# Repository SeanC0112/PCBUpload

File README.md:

# PCBUpload
Upload of my PCB files for my quadruped robot

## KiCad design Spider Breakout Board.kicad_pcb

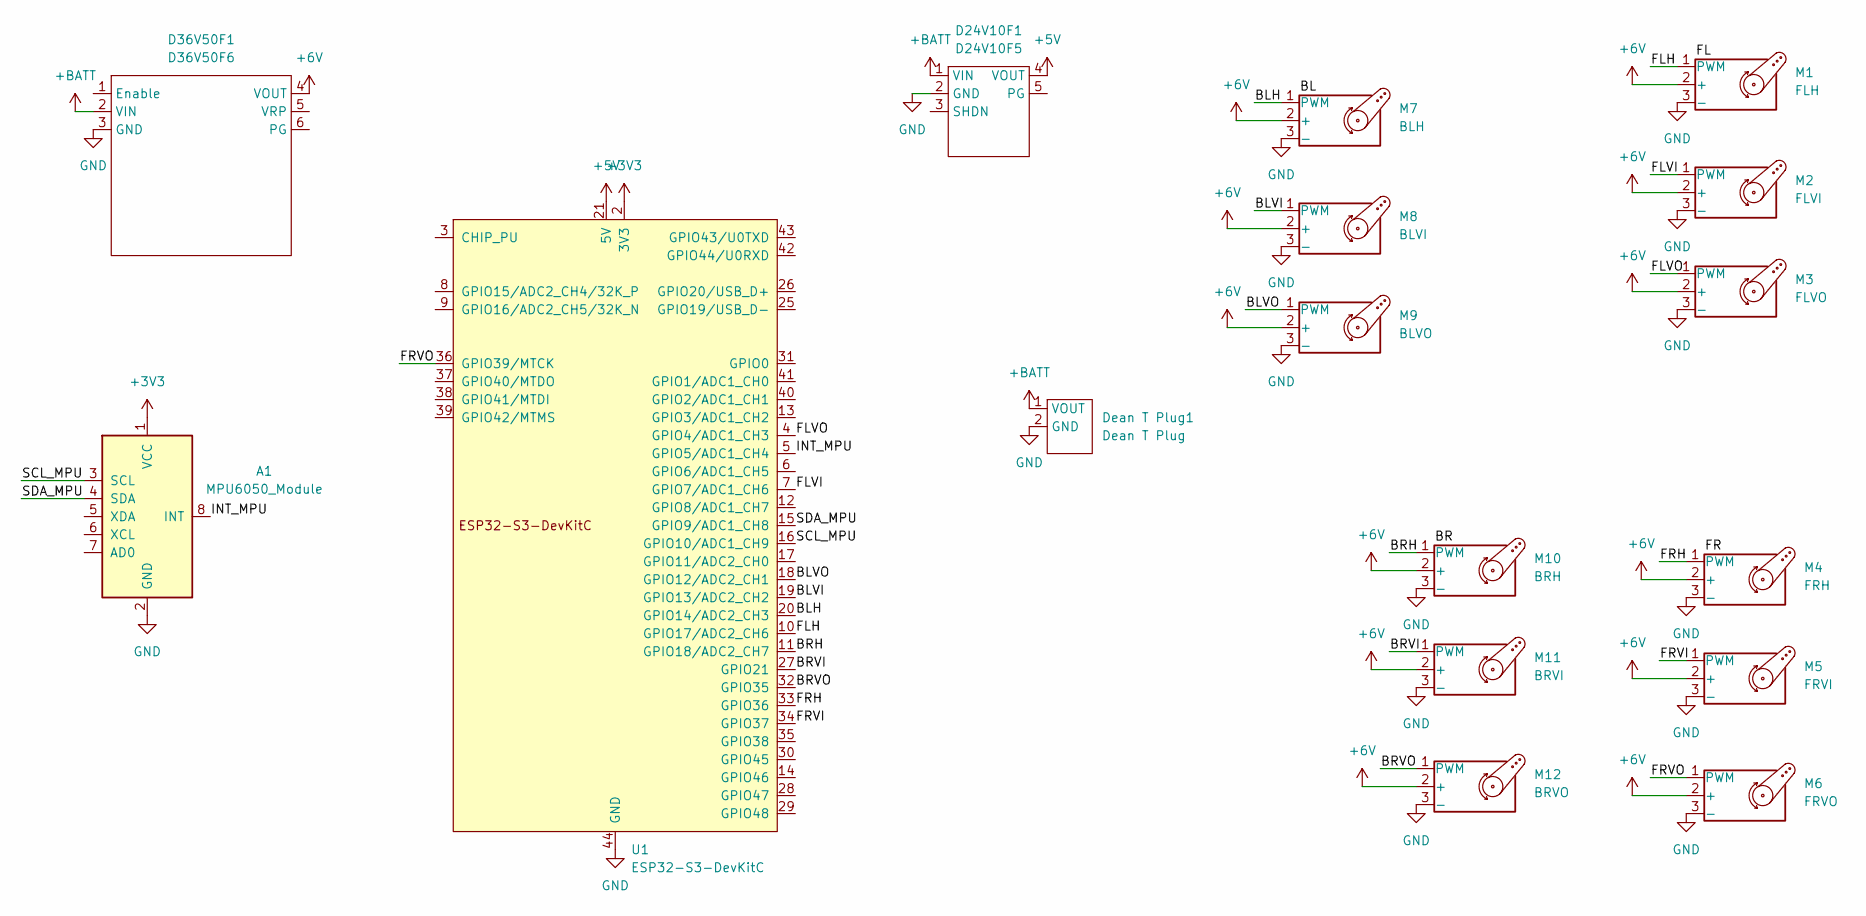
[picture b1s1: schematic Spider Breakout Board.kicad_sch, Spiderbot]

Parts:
A1: MPU6050_Module
D24V10F1: D24V10F5
D36V50F1: D36V50F6
Dean T Plug1: Dean T Plug; DEANS
M1: FLH; PinHeader_1x03_P2.54mm_Vertical
M2: FLVI; PinHeader_1x03_P2.54mm_Vertical
M3: FLVO; PinHeader_1x03_P2.54mm_Vertical
M4: FRH; PinHeader_1x03_P2.54mm_Vertical
M5: FRVI; PinHeader_1x03_P2.54mm_Vertical
M6: FRVO; PinHeader_1x03_P2.54mm_Vertical
M7: BLH; PinHeader_1x03_P2.54mm_Vertical
M8: BLVI; PinHeader_1x03_P2.54mm_Vertical
M9: BLVO; PinHeader_1x03_P2.54mm_Vertical
M10: BRH; PinHeader_1x03_P2.54mm_Vertical
M11: BRVI; PinHeader_1x03_P2.54mm_Vertical
M12: BRVO; PinHeader_1x03_P2.54mm_Vertical
U1: ESP32-S3-DevKitC

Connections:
+3V3: A1.1 (VCC), U1.1 (3V3), U1.2 (3V3)
+5V: D24V10F1.4 (VOUT), U1.21 (5V)
+6V: D36V50F1.4 (VOUT), M1.2 (+), M2.2 (+), M3.2 (+), M4.2 (+), M5.2 (+), M6.2 (+), M7.2 (+), M8.2 (+), M9.2 (+), M10.2 (+), M11.2 (+), M12.2 (+)
+BATT: D24V10F1.1 (VIN), D36V50F1.2 (VIN), Dean T Plug1.1 (VOUT)
/BLH: M7.1 (PWM), U1.20 (GPIO14/ADC2_CH3)
/BLVI: M8.1 (PWM), U1.19 (GPIO13/ADC2_CH2)
/BLVO: M9.1 (PWM), U1.18 (GPIO12/ADC2_CH1)
/BRH: M10.1 (PWM), U1.11 (GPIO18/ADC2_CH7)
/BRVI: M11.1 (PWM), U1.27 (GPIO21)
/BRVO: M12.1 (PWM), U1.32 (GPIO35)
/FLH: M1.1 (PWM), U1.10 (GPIO17/ADC2_CH6)
/FLVI: M2.1 (PWM), U1.7 (GPIO7/ADC1_CH6)
/FLVO: M3.1 (PWM), U1.4 (GPIO4/ADC1_CH3)
/FRH: M4.1 (PWM), U1.33 (GPIO36)
/FRVI: M5.1 (PWM), U1.34 (GPIO37)
/FRVO: M6.1 (PWM), U1.36 (GPIO39/MTCK)
/INT_MPU: A1.8 (INT), U1.5 (GPIO5/ADC1_CH4)
/SCL_MPU: A1.3 (SCL), U1.16 (GPIO10/ADC1_CH9)
/SDA_MPU: A1.4 (SDA), U1.15 (GPIO9/ADC1_CH8)
GND: A1.2 (GND), D24V10F1.2 (GND), D36V50F1.3 (GND), Dean T Plug1.2 (GND), M1.3 (-), M2.3 (-), M3.3 (-), M4.3 (-), M5.3 (-), M6.3 (-), M7.3 (-), M8.3 (-), M9.3 (-), M10.3 (-), M11.3 (-), M12.3 (-), U1.22 (GND), U1.23 (GND), U1.24 (GND), U1.44 (GND)

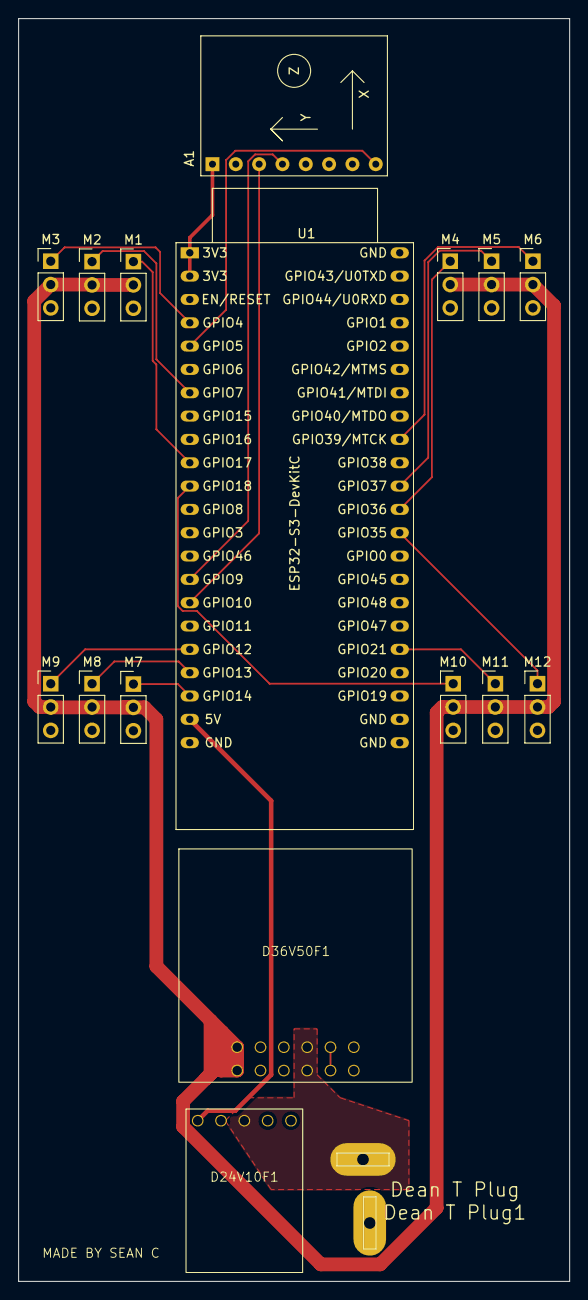
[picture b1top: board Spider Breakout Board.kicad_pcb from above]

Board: 2 copper layers, 60.0 x 137.5 mm, 17 parts (0 on the bottom side), 20 nets.
